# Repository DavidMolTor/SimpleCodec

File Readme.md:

# PICO FX

A simple stereo guitar effects platform using an RP Pico 2 development board.

## Introduction

This module is designed to be used as a development platform for guitar effects running on the RP2350 architecture.

The module contains a CS4272 codec with stereo inputs and outputs. It also includes a set of clean buffers to match the guitar and other effects in the chain.

All the power regulation is done through LDO regulators that prioritize low ripple in exchange for worse efficiency.

It is designed to work with 9V intput voltage. It also has a set of headers for it to be able to interface with a control board in the future.

## Features

 - Clear separation between digital and analog sections.

 - Stereo input and output.

 - Clean voltage delivery.

 - Flexible interface for controls.

 - Easy future development.

 - Afforable BOM.

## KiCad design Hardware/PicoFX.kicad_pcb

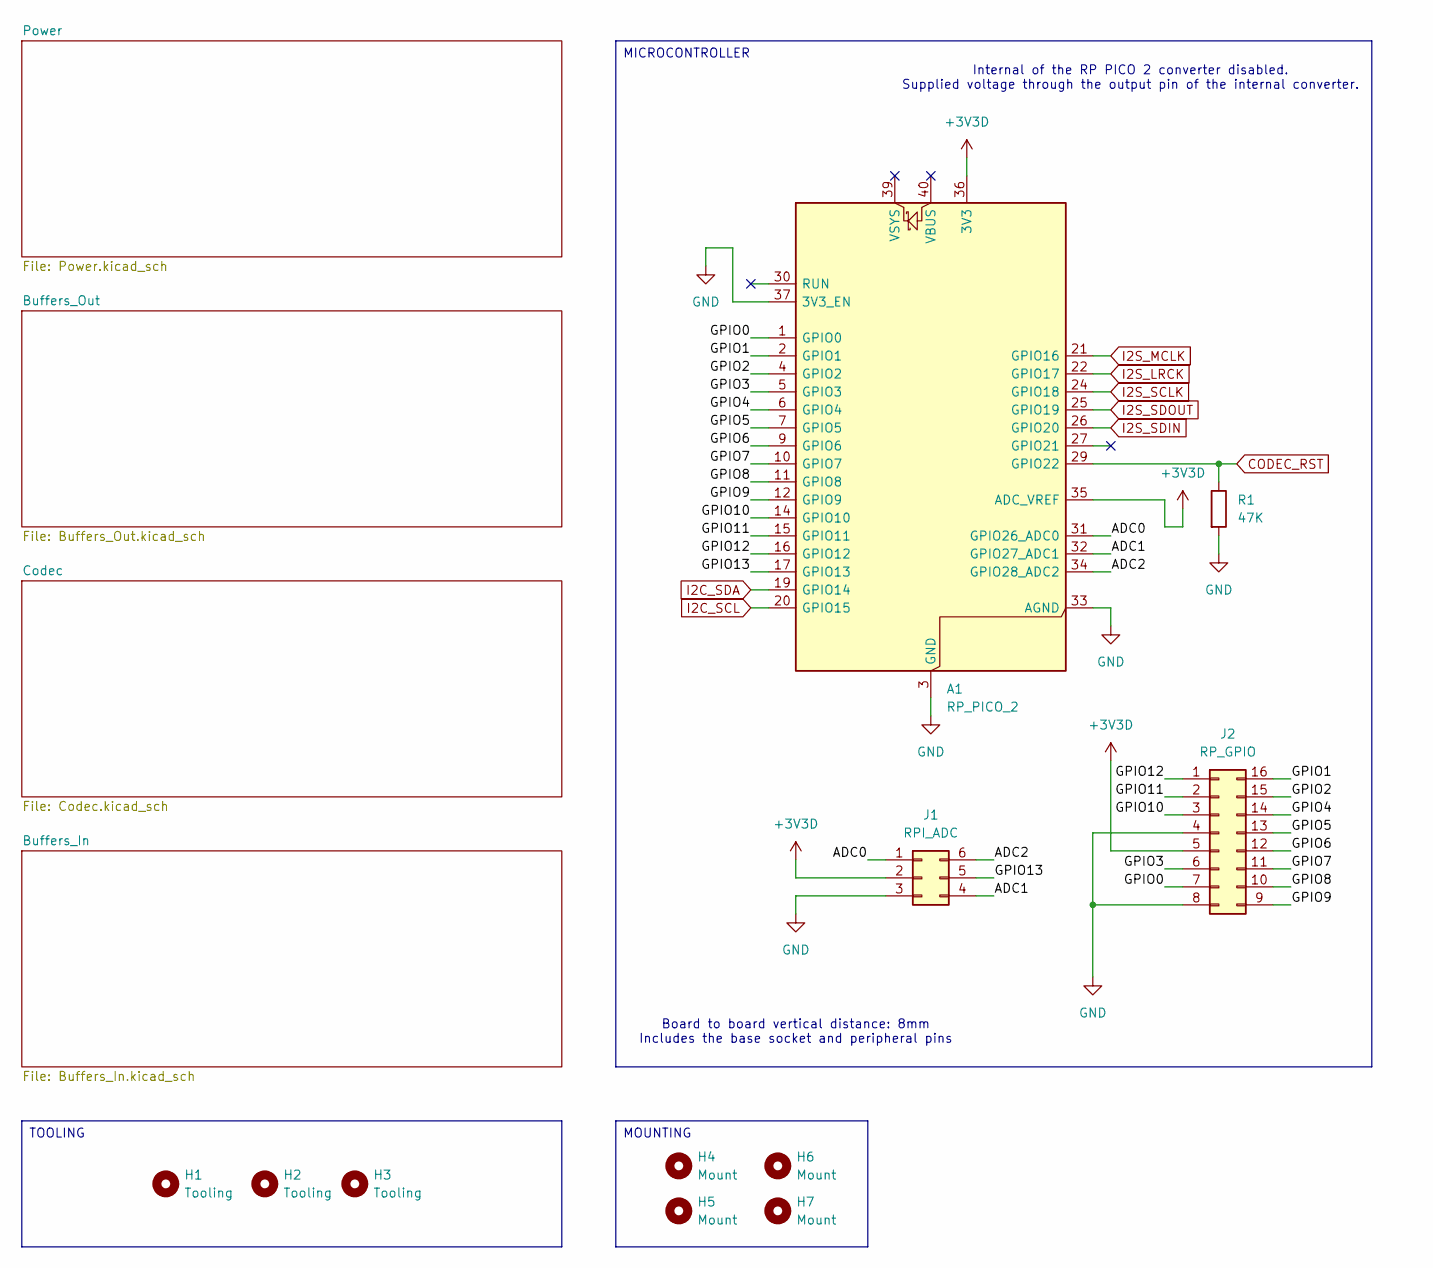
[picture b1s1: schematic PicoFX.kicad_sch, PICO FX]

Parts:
A1: RP_PICO_2; RP_PICO_2_SMD
H1, H2, H3: Tooling; ToolingHole_1.152mm
H4, H5, H6, H7: Mount; MountingHole_2.2mm_M2
J1: RPI_ADC; HEADER_THROUGH_2x03_P2.54mm
J2: RP_GPIO; HEADER_THROUGH_2x08_P2.54mm
R1: 47K; R_0603_1608Metric

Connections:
+3V3D: A1.35 (ADC_VREF), A1.36 (3V3), J1.2, J2.5; also elsewhere on the board
/ADC0: A1.31 (GPIO26_ADC0), J1.1
/ADC1: A1.32 (GPIO27_ADC1), J1.4
/ADC2: A1.34 (GPIO28_ADC2), J1.6
/GPIO0: A1.1 (GPIO0), J2.7
/GPIO1: A1.2 (GPIO1), J2.16
/GPIO2: A1.4 (GPIO2), J2.15
/GPIO3: A1.5 (GPIO3), J2.6
/GPIO4: A1.6 (GPIO4), J2.14
/GPIO5: A1.7 (GPIO5), J2.13
/GPIO6: A1.9 (GPIO6), J2.12
/GPIO7: A1.10 (GPIO7), J2.11
/GPIO8: A1.11 (GPIO8), J2.10
/GPIO9: A1.12 (GPIO9), J2.9
/GPIO10: A1.14 (GPIO10), J2.3
/GPIO11: A1.15 (GPIO11), J2.2
/GPIO12: A1.16 (GPIO12), J2.1
/GPIO13: A1.17 (GPIO13), J1.5
CODEC_RST: A1.29 (GPIO22), R1.1; also elsewhere on the board
GND: A1.3 (GND), A1.8 (GND), A1.13 (GND), A1.18 (GND), A1.23 (GND), A1.28 (GND), A1.33 (AGND), A1.37 (3V3_EN), A1.38 (GND), J1.3, J2.4, J2.8, R1.2; also elsewhere on the board
I2C_SCL: A1.20 (GPIO15); also elsewhere on the board
I2C_SDA: A1.19 (GPIO14); also elsewhere on the board
I2S_LRCK: A1.22 (GPIO17); also elsewhere on the board
I2S_MCLK: A1.21 (GPIO16); also elsewhere on the board
I2S_SCLK: A1.24 (GPIO18); also elsewhere on the board
I2S_SDIN: A1.26 (GPIO20); also elsewhere on the board
I2S_SDOUT: A1.25 (GPIO19); also elsewhere on the board

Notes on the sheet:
Board to board vertical distance: 8mm Includes the base socket and peripheral pins
Internal of the RP PICO 2 converter disabled. Supplied voltage through the output pin of the internal converter.
MICROCONTROLLER
TOOLING
MOUNTING

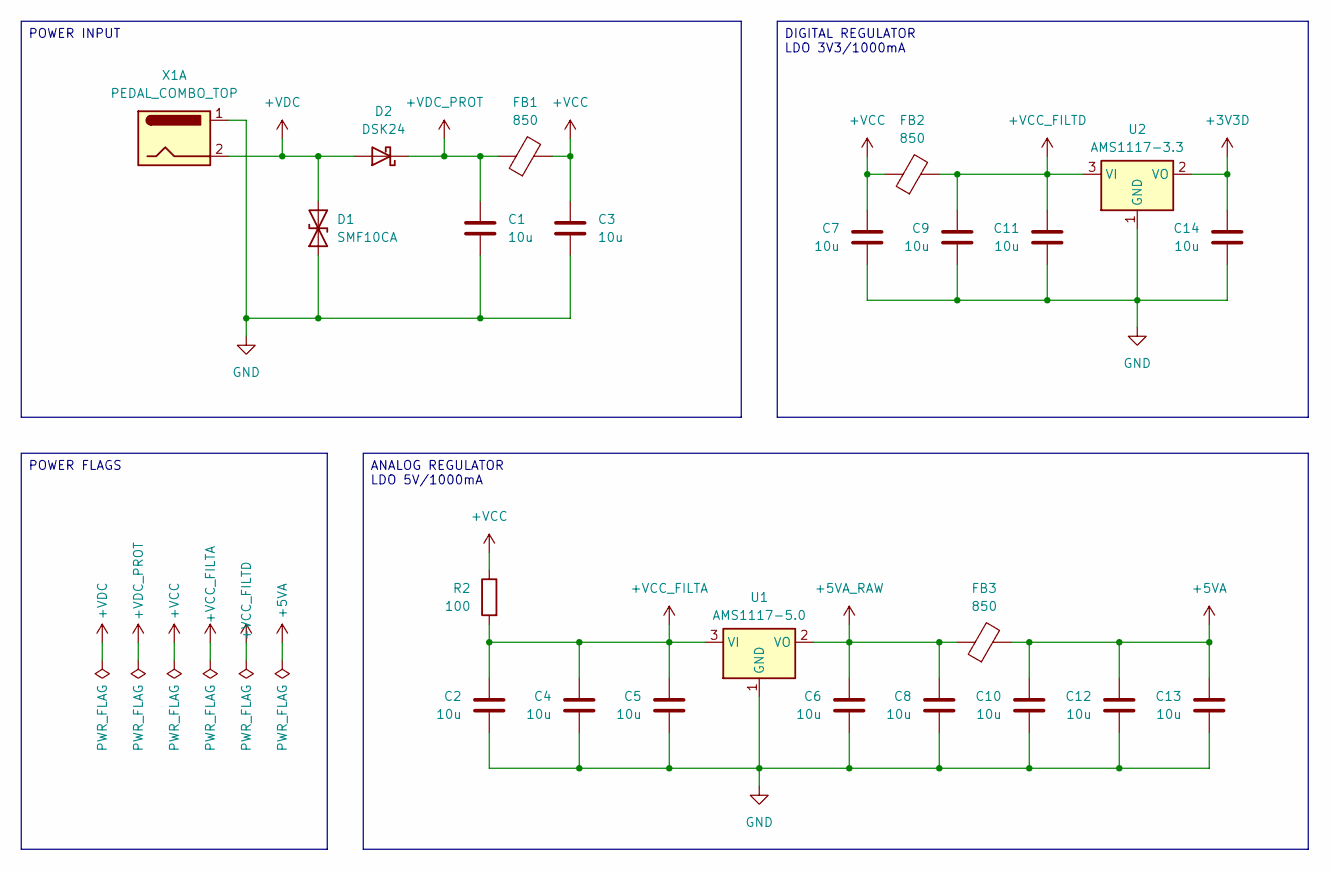
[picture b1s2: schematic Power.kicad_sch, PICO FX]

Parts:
C1, C2, C3, C4, C5, C6, C7, C8, C9, C10, C11, C12, C13, C14: 10u; C_0805_2012Metric
D1: SMF10CA; D_SOD-123F
D2: DSK24; D_SOD-123F
FB1, FB2, FB3: 850; L_0603_1608Metric
R2: 100; R_0603_1608Metric
U1: AMS1117-5.0; SOT-223-3_TabPin2
U2: AMS1117-3.3; SOT-223-3_TabPin2
X1: PEDAL_COMBO_TOP

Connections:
+3V3D: C14.1, U2.2 (VO); also elsewhere on the board
+5VA: C10.1, C12.1, C13.1, FB3.2; also elsewhere on the board
+5VA_RAW: C6.1, C8.1, FB3.1, U1.2 (VO)
+VCC: C3.1, C7.1, FB1.2, FB2.1, R2.1
+VCC_FILTA: C2.1, C4.1, C5.1, R2.2, U1.3 (VI)
+VCC_FILTD: C9.1, C11.1, FB2.2, U2.3 (VI)
+VDC: D1.2 (A2), D2.2 (A), X1.2
+VDC_PROT: C1.1, D2.1 (K), FB1.1
GND: C1.2, C2.2, C3.2, C4.2, C5.2, C6.2, C7.2, C8.2, C9.2, C10.2, C11.2, C12.2, C13.2, C14.2, D1.1 (A1), U1.1 (GND), U2.1 (GND), X1.1; also elsewhere on the board

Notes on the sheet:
DIGITAL REGULATOR LDO 3V3/1000mA
POWER INPUT
ANALOG REGULATOR LDO 5V/1000mA
POWER FLAGS

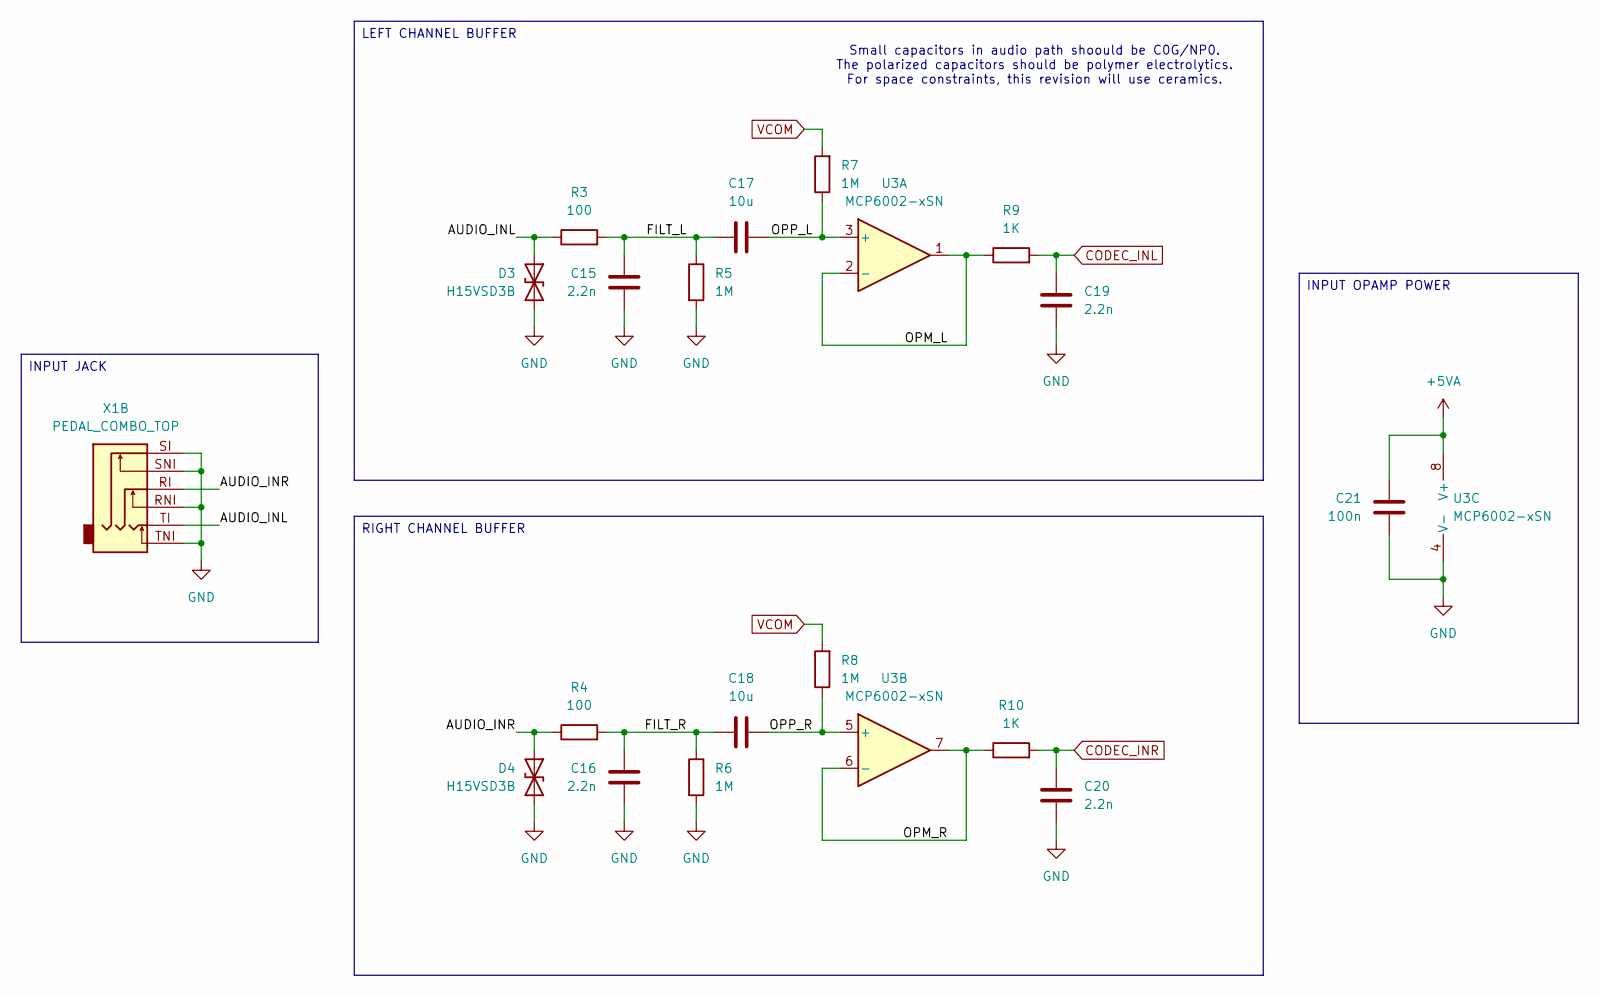
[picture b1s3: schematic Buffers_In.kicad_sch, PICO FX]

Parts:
C15, C16, C19, C20: 2.2n; C_0805_2012Metric
C17, C18: 10u; C_0805_2012Metric
C21: 100n; C_0603_1608Metric
D3, D4: H15VSD3B; D_SOD-323
R3, R4: 100; R_0603_1608Metric
R5, R6, R7, R8: 1M; R_0603_1608Metric
R9, R10: 1K; R_0603_1608Metric
U3: MCP6002-xSN; SOIC-8_3.9x4.9mm_P1.27mm
X1: PEDAL_COMBO_TOP

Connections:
+5VA: C21.1, U3.8 (V+); also elsewhere on the board
/Buffers_In/AUDIO_INL: D3.1 (A1), R3.1, X1.TI
/Buffers_In/AUDIO_INR: D4.1 (A1), R4.1, X1.RI
/Buffers_In/FILT_L: C15.2, C17.1, R3.2, R5.1
/Buffers_In/FILT_R: C16.2, C18.1, R4.2, R6.1
/Buffers_In/OPM_L: R9.1, U3.1, U3.2 (-)
/Buffers_In/OPM_R: R10.1, U3.6 (-), U3.7
/Buffers_In/OPP_L: C17.2, R7.1, U3.3 (+)
/Buffers_In/OPP_R: C18.2, R8.1, U3.5 (+)
CODEC_INL: C19.1, R9.2; also elsewhere on the board
CODEC_INR: C20.1, R10.2; also elsewhere on the board
GND: C15.1, C16.1, C19.2, C20.2, C21.2, D3.2 (A2), D4.2 (A2), R5.2, R6.2, U3.4 (V-), X1.RNI, X1.SI, X1.SNI, X1.TNI; also elsewhere on the board
VCOM: R7.2, R8.2; also elsewhere on the board

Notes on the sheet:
Small capacitors in audio path shoould be C0G/NP0. The polarized capacitors should be polymer electrolytics. For space constraints, this revision will use ceramics.
LEFT CHANNEL BUFFER
INPUT OPAMP POWER
INPUT JACK
RIGHT CHANNEL BUFFER

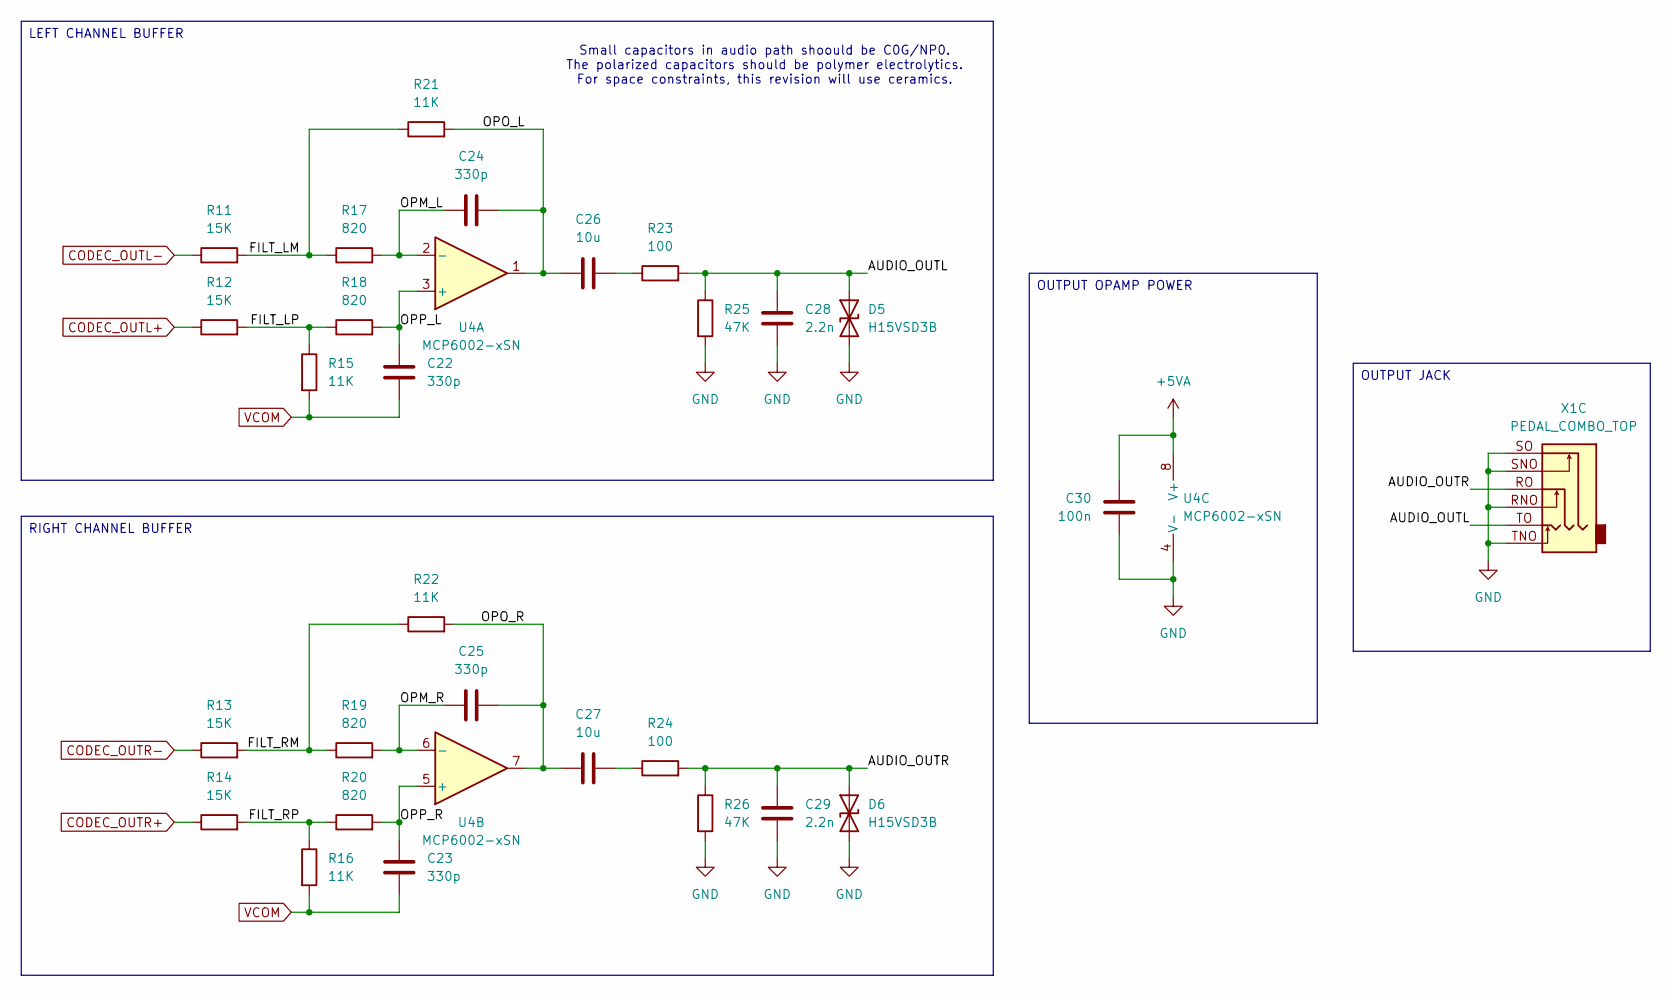
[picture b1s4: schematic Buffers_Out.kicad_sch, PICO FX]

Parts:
C22, C23, C24, C25: 330p; C_0603_1608Metric
C26, C27: 10u; C_0805_2012Metric
C28, C29: 2.2n; C_0805_2012Metric
C30: 100n; C_0603_1608Metric
D5, D6: H15VSD3B; D_SOD-323
R11, R12, R13, R14: 15K; R_0603_1608Metric
R15, R16, R21, R22: 11K; R_0603_1608Metric
R17, R18, R19, R20: 820; R_0603_1608Metric
R23, R24: 100; R_0603_1608Metric
R25, R26: 47K; R_0603_1608Metric
U4: MCP6002-xSN; SOIC-8_3.9x4.9mm_P1.27mm
X1: PEDAL_COMBO_TOP

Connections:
+5VA: C30.1, U4.8 (V+); also elsewhere on the board
/Buffers_Out/AUDIO_OUTL: C28.1, D5.1 (A1), R23.2, R25.1, X1.TO
/Buffers_Out/AUDIO_OUTR: C29.1, D6.1 (A1), R24.2, R26.1, X1.RO
/Buffers_Out/FILT_LM: R11.2, R17.1, R21.1
/Buffers_Out/FILT_LP: R12.2, R15.1, R18.1
/Buffers_Out/FILT_RM: R13.2, R19.1, R22.1
/Buffers_Out/FILT_RP: R14.2, R16.1, R20.1
/Buffers_Out/OPM_L: C24.1, R17.2, U4.2 (-)
/Buffers_Out/OPM_R: C25.1, R19.2, U4.6 (-)
/Buffers_Out/OPO_L: C24.2, C26.1, R21.2, U4.1
/Buffers_Out/OPO_R: C25.2, C27.1, R22.2, U4.7
/Buffers_Out/OPP_L: C22.1, R18.2, U4.3 (+)
/Buffers_Out/OPP_R: C23.1, R20.2, U4.5 (+)
CODEC_OUTL+: R12.1; also elsewhere on the board
CODEC_OUTL-: R11.1; also elsewhere on the board
CODEC_OUTR+: R14.1; also elsewhere on the board
CODEC_OUTR-: R13.1; also elsewhere on the board
GND: C28.2, C29.2, C30.2, D5.2 (A2), D6.2 (A2), R25.2, R26.2, U4.4 (V-), X1.RNO, X1.SNO, X1.SO, X1.TNO; also elsewhere on the board
unnamed: C26.2, R23.1
unnamed: C27.2, R24.1
VCOM: C22.2, C23.2, R15.2, R16.2; also elsewhere on the board

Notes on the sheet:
Small capacitors in audio path shoould be C0G/NP0. The polarized capacitors should be polymer electrolytics. For space constraints, this revision will use ceramics.
OUTPUT JACK
LEFT CHANNEL BUFFER
RIGHT CHANNEL BUFFER
OUTPUT OPAMP POWER

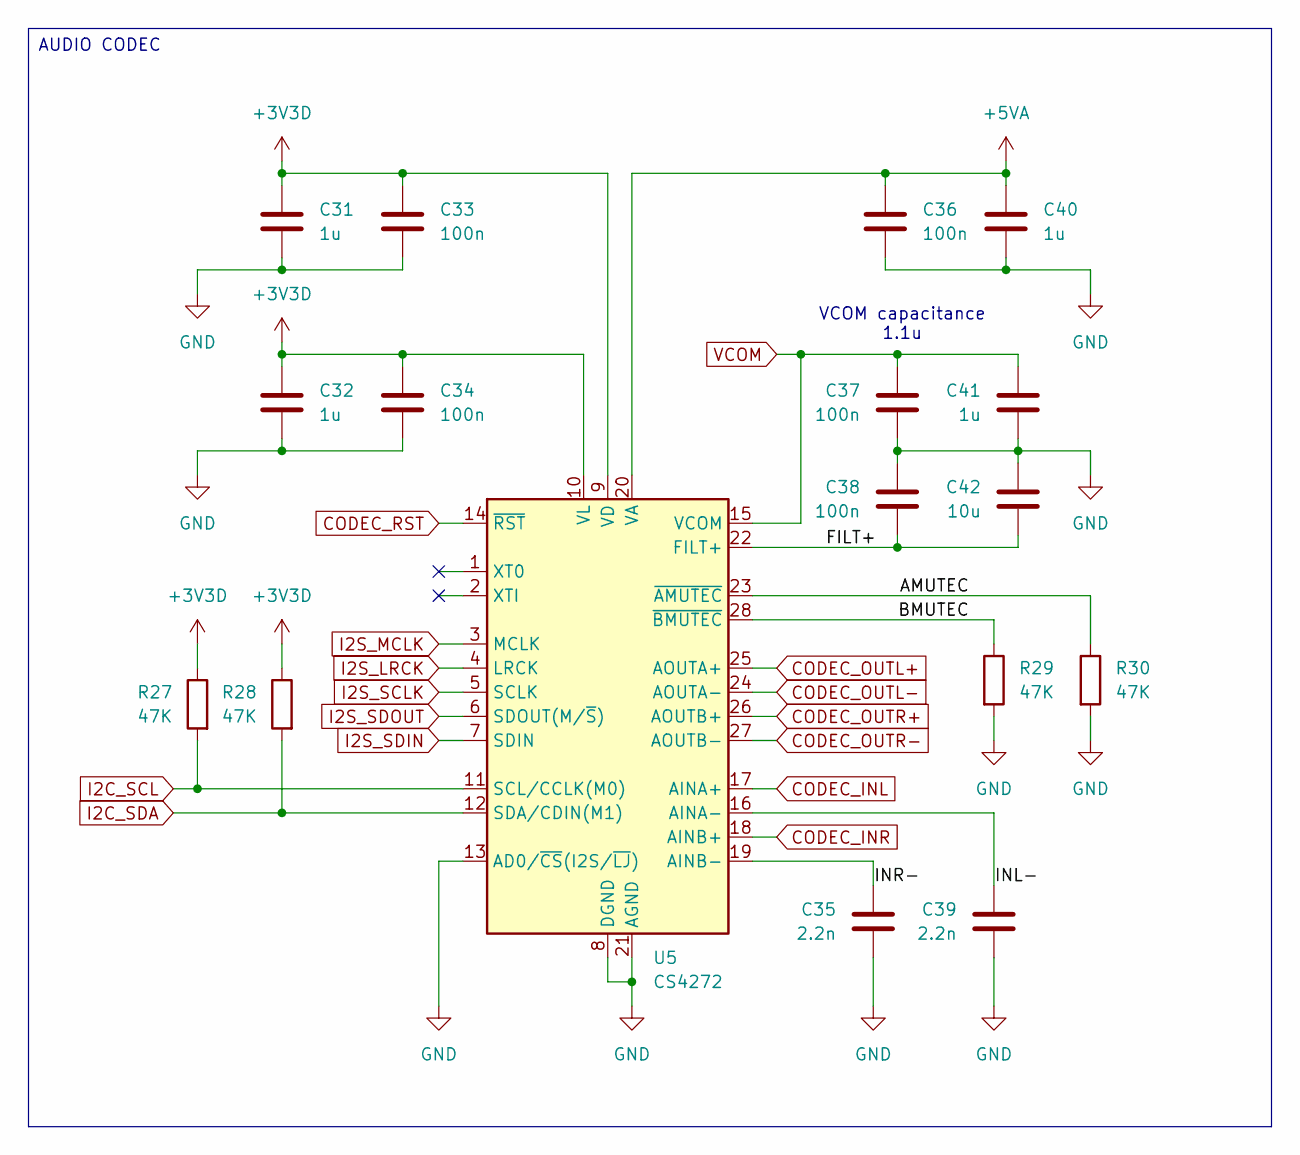
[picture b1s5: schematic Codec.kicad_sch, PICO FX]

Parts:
C31, C32, C40, C41: 1u; C_0805_2012Metric
C33, C34, C36, C37, C38: 100n; C_0603_1608Metric
C35, C39: 2.2n; C_0805_2012Metric
C42: 10u; C_0805_2012Metric
R27, R28, R29, R30: 47K; R_0603_1608Metric
U5: CS4272; TSSOP-28_4.4x9.7mm_P0.65mm

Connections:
+3V3D: C31.2, C32.2, C33.1, C34.1, R27.1, R28.1, U5.9 (VD), U5.10 (VL); also elsewhere on the board
+5VA: C36.2, C40.1, U5.20 (VA); also elsewhere on the board
/Codec/AMUTEC: R30.1, U5.23 (~AMUTEC)
/Codec/BMUTEC: R29.1, U5.28 (~BMUTEC)
/Codec/FILT+: C38.1, C42.2, U5.22 (FILT+)
/Codec/INL-: C39.1, U5.16 (AINA-)
/Codec/INR-: C35.1, U5.19 (AINB-)
CODEC_INL: U5.17 (AINA+); also elsewhere on the board
CODEC_INR: U5.18 (AINB+); also elsewhere on the board
CODEC_OUTL+: U5.25 (AOUTA+); also elsewhere on the board
CODEC_OUTL-: U5.24 (AOUTA-); also elsewhere on the board
CODEC_OUTR+: U5.26 (AOUTB+); also elsewhere on the board
CODEC_OUTR-: U5.27 (AOUTB-); also elsewhere on the board
CODEC_RST: U5.14 (~RST); also elsewhere on the board
GND: C31.1, C32.1, C33.2, C34.2, C35.2, C36.1, C37.2, C38.2, C39.2, C40.2, C41.2, C42.1, R29.2, R30.2, U5.8 (DGND), U5.13 (AD0/~CS(I2S/~LJ)), U5.21 (AGND); also elsewhere on the board
I2C_SCL: R27.2, U5.11 (SCL/CCLK(M0)); also elsewhere on the board
I2C_SDA: R28.2, U5.12 (SDA/CDIN(M1)); also elsewhere on the board
I2S_LRCK: U5.4 (LRCK); also elsewhere on the board
I2S_MCLK: U5.3 (MCLK); also elsewhere on the board
I2S_SCLK: U5.5 (SCLK); also elsewhere on the board
I2S_SDIN: U5.7 (SDIN); also elsewhere on the board
I2S_SDOUT: U5.6 (SDOUT(M/~S)); also elsewhere on the board
VCOM: C37.1, C41.1, U5.15 (VCOM); also elsewhere on the board

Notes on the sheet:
VCOM capacitance 1.1u
AUDIO CODEC

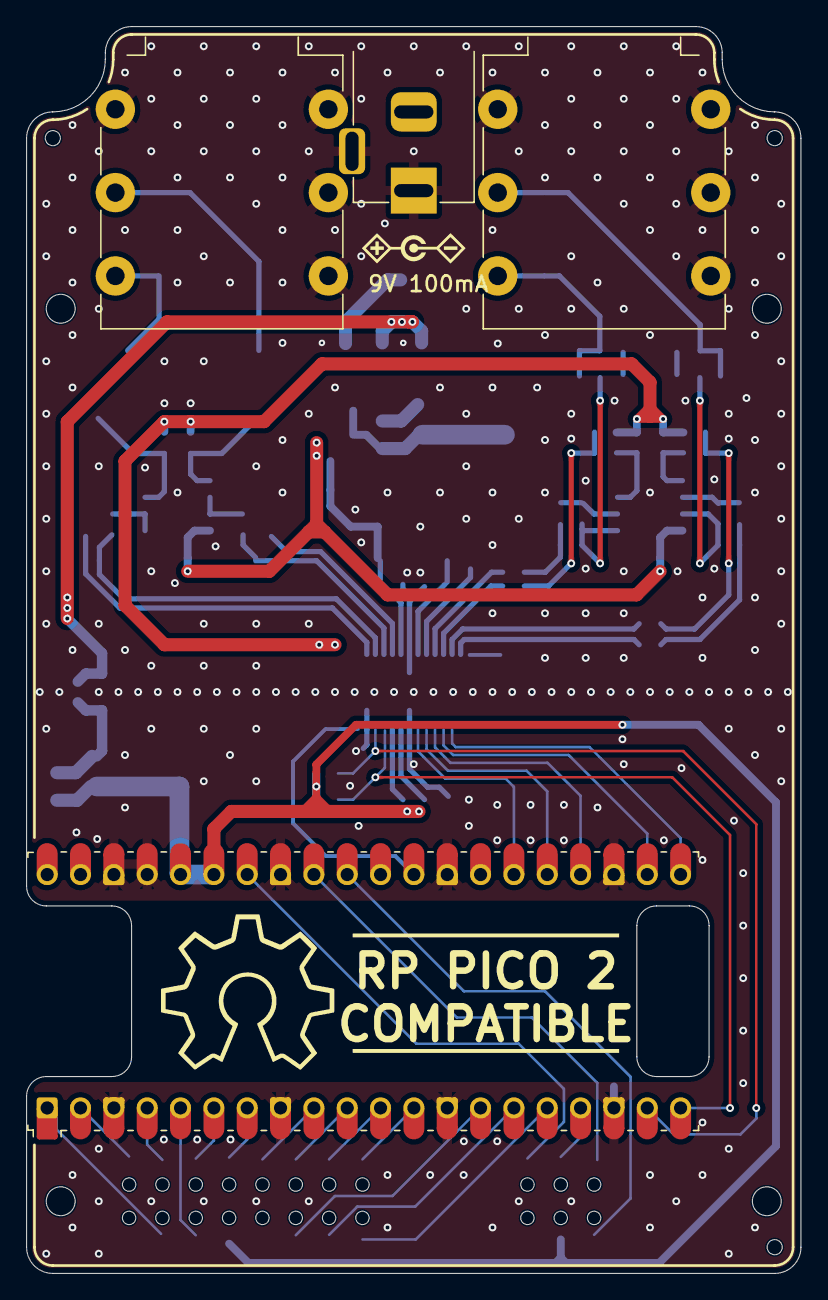
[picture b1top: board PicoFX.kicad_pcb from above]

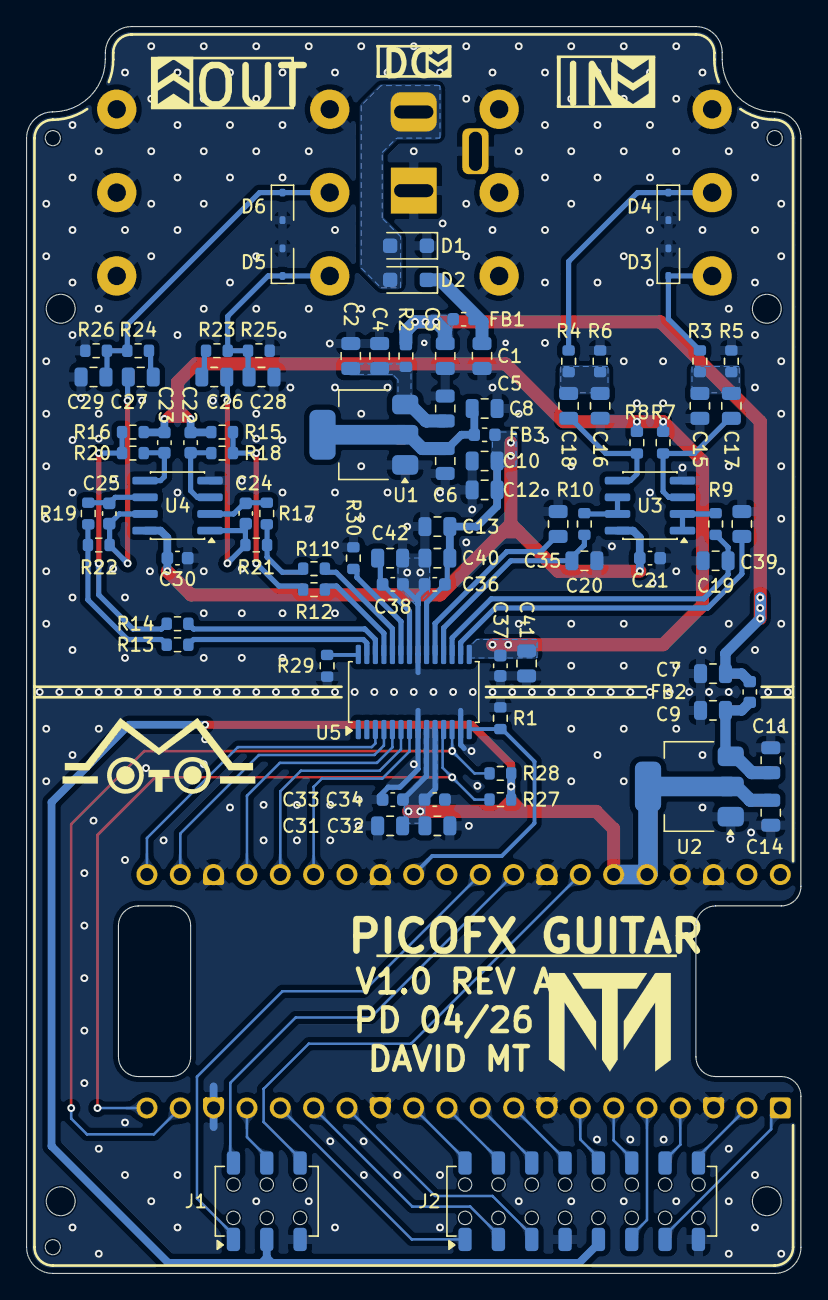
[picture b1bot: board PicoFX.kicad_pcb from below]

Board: 4 copper layers, 59.0 x 95.0 mm, 97 parts (92 on the bottom side), 68 nets.

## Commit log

2026-04-09 Readme file
    Added a readme file to the project.
2026-04-09 Schematic
    Updated the schematic.
    Added the codec schematic module.
    Added the buffer schematic module.
    Added the RP2350 schematic module.
2026-04-10 Schematic
    Updated the power delivery module.
    Other minor changes.
2026-04-12 Moved to a CS4272 codec as a cheaper alternative with similar performance.
2026-04-12 Initial layout
    Initial layout inside a 1590N1/125B pedal enclosure.
2026-04-13 RP2350 layout
    Updated the layout for the RP2350.
    Added board headers.
2026-04-15 Input buffer and power
    Updated the input buffer layout.
    Updated the power supply layout.
2026-04-15 Codec layout
    Updated the codec layout.
2026-04-15 Missing connections
    Updated the board layout.
    Added al missing connections.
2026-04-16 Initial mounting holes
    Added some minimal mounting holes.
    Need to review the positioning.
2026-04-16 Silkscreen design
    Updated the silkscreen for the PCB.
2026-04-18 Build materials
    Uploaded all files required for assembly.
2026-04-18 Project description
    Updated the project description.
2026-04-19 Silkscreen and notes
    Updated the board silkscreen.
    Updated VCOM capacitance value.
2026-04-19 Silkscreen and build
    Updated the silkscreen of the PCB.
    Updated all build files.
2026-04-21 Silkscreen logos
    Addedd some logos to the silkscreen layer.
2026-04-25 Layout revision
    Minor updated to references.
    Minor updated to the PCB layout.
2026-04-25 Layout optimization
    Optimized the PCB layout.
2026-04-25 Output files
    Updated the build files.
2026-04-25 Redme file
    Updated the readme file.
